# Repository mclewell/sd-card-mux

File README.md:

# SD-Card-Mux
A tool to automate testing SD-Card images on embedded devices.

When developing images for embedded devices, do you often find yourself 
constanly moving the SD-Card between the embedded device and development
computer? Surely there is a way to automate this switching...

The SD-Card Mux sits between the host development computer and an
embedded device, such as a Beaglebone Black, and allows an SD-Card to be 
programatically switched between the two.

The board uses a USB hub (U2640) that contains an SD-Card/MMC interface. A
standard micro-SD Card connects to this interface. One of the other USB ports 
on the hub connects to a USB-UART bridge (CP2102N). This bridge prodives a UART 
interface to the DUT and also controls the switching on the mux (TS3A27518E) 
using the GPIO on the bridge. The GPIO is controlled by the host computer 
using ```libgpiod```. 

Normally, the SD-Card is connected to the host computer. An image that is to be
booted by the DUT is written to the SD-Card. Instead of manually removing the 
card and inserting it into the DUT, a simple script can be added to the 
software development tooling to switch the card from the host computer to the 
embedded DUT.

## Usage
The SD-Card-Mux switching can be either controlled via software or manually
using the switch (```SW1```) on the top of the board.

### Software Control
Prerequisite: ```libgpiod```

Ubuntu:
```
sudo apt install libgpiod libgpiod-dev
```

Arch: Install from the AUR: 
```
https://aur.archlinux.org/packages/libgpiod/
```

1. Set SW2 (bottom left corner) to 'HW'. (**Note:** Silkscreen labels
on the board are backwards)
2. Insert a micro-sd card into J4.
3. Insert the sd-card-mux into the micro-sd card slot of the development board.
4. Connect a micro-USB cable between the sd-card-mux and development PC.
5. On power-up the sd-card-mux will route the SD card to the DUT, as denoted by the
illuminated LED by the micro-sd protrusion.
6. To switch the SD card to the development PC:
	
	6a. Find the GPIO controller name of the CP210N:
	```
	$ sudo gpiodetect
	gpiochip0 [INT34BB:00] (312 lines)
	gpiochip1 [cp210x] (4 lines)
	```
	6b. The mux control line is on ```GPIO.0```. To switch,
	```
	$ sudo gpioset gpiochip1 0=0
	```
	The LED next to the micro-sd card slot will blink when the SD-Card is
	accessed.

#### UART and Additional GPIO
The SD-Card-Mux also contains a USB-UART serial bridge. Conect the ```TXD```
and ```RXD``` signals in J2 to the UART on the DUT. The bridge should appear
on the development computer as ```/dev/ttyUSB0```.

There are also two additional GPIO from the CP210N broken out into the J2 
header (```GPIO.2```, ```GPIO.3```). These signals can be controlled in the same
fashion as the mux switch function using ```gpioset```. One of these lines can
be connected to the reset of the DUT. Ideally, the DUT should be held in reset
while the SD-card is switched. Once switched over, the reset line can be released
allowing the DUT to boot the new image. 

### Manual Control
1. Set SW2 to the 'SW' position. (**Note:** Silkscreen labels on the board are
backwards)
2. Use SW1 to switch the micro-SD card between the DUT and development 
computer. (**Note:** the silkscreen labels are also backwards here).

# Acknowledgements
- https://wiki.tizen.org/SDWire
- https://github.com/kopasiak/sd-mux

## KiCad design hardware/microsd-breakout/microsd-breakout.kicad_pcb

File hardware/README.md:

# Development Features
Since this was the first hardware spin of the board, some
development features were included.

## Software Switching
The software switching controlled through the CP210N GPIO control
the enable lines of two high-side power switches (```U7```/```U8```).
Only one of these switches should be enabled at a time, therefore the 
complementary output of ```U10``` is used. I had concerns that there
wouldn't be enough 'downtime' during the switch event to allow the 
on-board micro-sd card to fully powerdown before switching. 

The ```U10``` mux can be bypassed by using a GPIO.1 on the CP201N as 
the complementary switching singal. 
- Remove ```R12``` and ```R23```
- Install ```R11``` and ```R22```

During my testing, I have not seen any issues using the single mux
switch control line and mux complementary out.

## DUT Connection via FFC
A Flex-Flex Cable (FFC) header (```J3```) is provided to allow connections
to the DUT via a flex cable. The other end of the cable is connected to a
micro-sd breakout board, which is provided in this repo 
[here](microsd-breakout).

# Known Issues
- Silkscreen labels on ```S1``` and ```SW2``` are reversed.
- On-board micro-sd card in ```J4``` protrudes over the board edge
and may interfer with the DUT.
- The USB ESD protection (```D1```) caused the USB hub to fail to enumerate
at high-speed modes, full-speed works correctly. Removing ```D1``` solves
this issue.

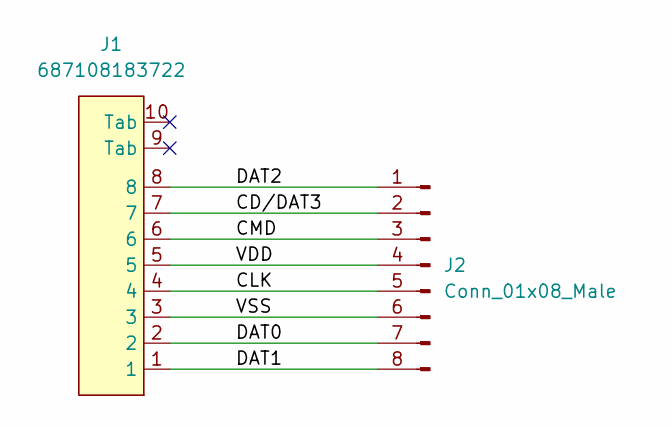
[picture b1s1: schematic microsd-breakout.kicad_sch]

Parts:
J1: 687108183722; Wurth_FPC_687108183722; PartNumber 687108183722
J2: Conn_01x08_Male; micro-sd-contacts

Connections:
/CD/DAT3: J1.7, J2.2
/CLK: J1.4, J2.5
/CMD: J1.6, J2.3
/DAT0: J1.2, J2.7
/DAT1: J1.1, J2.8
/DAT2: J1.8, J2.1
/VDD: J1.5, J2.4
/VSS: J1.3, J2.6

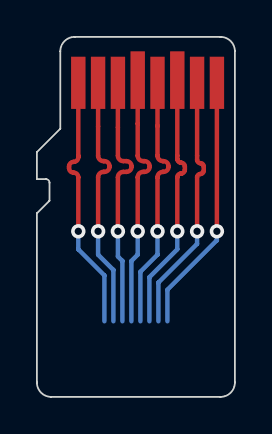
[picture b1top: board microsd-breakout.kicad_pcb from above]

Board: 2 copper layers, 11.0 x 20.0 mm, 3 parts (1 on the bottom side), 8 nets.

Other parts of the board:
REF1: Tab

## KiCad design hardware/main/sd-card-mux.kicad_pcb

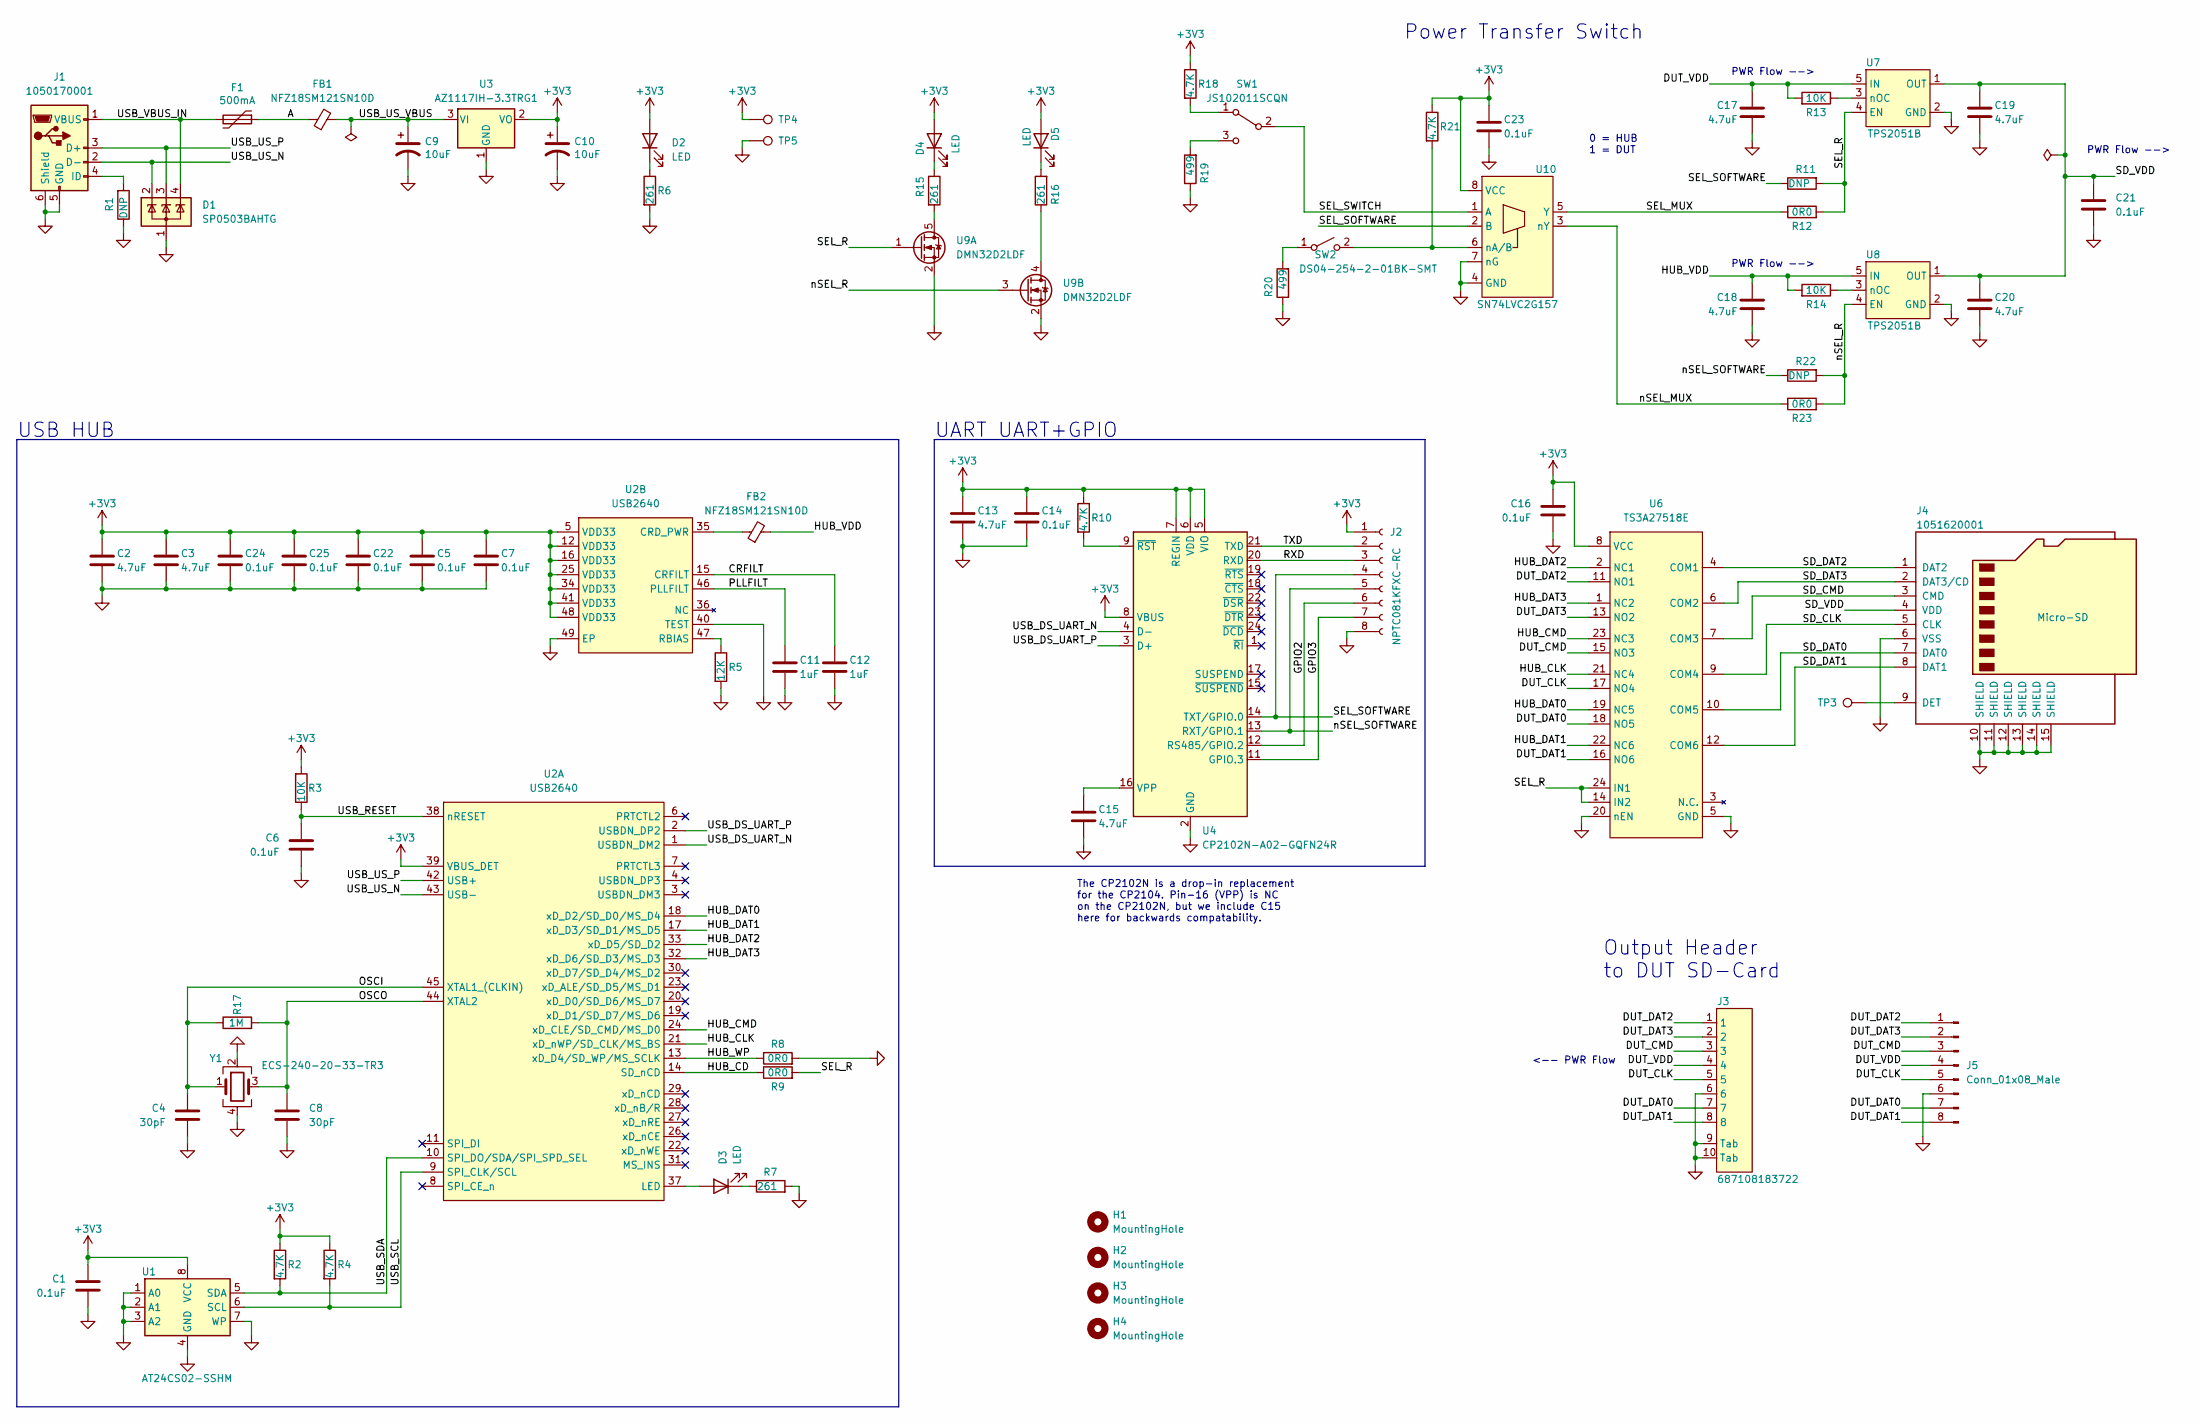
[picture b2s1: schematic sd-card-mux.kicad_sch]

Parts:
C1, C5, C6, C7, C14, C16, C21, C22, C23, C24, C25: 0.1uF; C_0603_1608Metric
C2, C3, C13, C15, C17, C18, C19, C20: 4.7uF; C_0603_1608Metric
C4, C8: 30pF; C_0603_1608Metric
C9, C10: 10uF; CP_EIA-3216-18_Kemet-A; PartNumber TAJA106K016SNJ
C11, C12: 1uF; C_0603_1608Metric
D1: SP0503BAHTG; SOT-143; PartNumber SP0503BAHTG
D2, D3, D4, D5: LED; LED_1206_3216Metric_Castellated
F1: 500mA; Fuse_1206_3216Metric_Castellated; PartNumber PTS120615V050
FB1, FB2: ‎NFZ18SM121SN10D‎; L_0603_1608Metric; PartNumber ‎NFZ18SM121SN10D‎
H1, H2, H3, H4: MountingHole; MountingHole_3.2mm_M3
J1: 1050170001; USB_Micro-B_Molex-105017-0001; PartNumber 1050170001
J2: NPTC081KFXC-RC; PinSocket_1x08_P2.54mm_Vertical_SMD_Pin1Right; PartNumber NPTC081KFXC-RC
J3: 687108183722; Wurth_FPC_687108183722; PartNumber 687108183722
J4: Micro-SD; micro-sd; PartNumber 1051620001
J5: Conn_01x08_Male; micro-sd-contacts
R1, R11, R22: DNP; R_0603_1608Metric
R2, R4, R10, R18, R21: 4.7K; R_0603_1608Metric
R3, R13, R14: 10K; R_0603_1608Metric
R5: 12K; R_0603_1608Metric
R6, R7, R15, R16: 261; R_0603_1608Metric
R8, R9, R12, R23: 0R0; R_0603_1608Metric
R17: 1M; R_0603_1608Metric
R19, R20: 499; R_0603_1608Metric
SW1: JS102011SCQN; CK_Switch_JS102011SCQN; PartNumber JS102011SCQN
SW2: DS04-254-2-01BK-SMT; CUI_DEVICES_DS04-254-2-01BK-SMT; PartNumber DS04-254-2-01BK-SMT
TP3: TestPoint; TestPoint_Pad_D1.0mm
TP4, TP5: TestPoint; test_point_RCSCTE; PartNumber RCSCTE
U1: AT24CS02-SSHM; SOIC-8_3.9x4.9mm_P1.27mm; PartNumber AT24CS02-SSHM-B
U2: USB2640; VQFN-48; PartNumber USB2640-HZH-02
U3: AZ1117IH-3.3TRG1; SOT-223-3_TabPin2; PartNumber AZ1117IH-3.3TRG1
U4: CP2102N-A02-GQFN24R; QFN-24-1EP_4x4mm_P0.5mm_EP2.6x2.6mm; PartNumber CP2102N-A02-GQFN24R
U6: TS3A27518E; TI_PW; PartNumber TS3A27518EPWR
U7, U8: TPS2051B; SOT-23-5; PartNumber TPS2051BDBVR
U9: DMN32D2LDF; SOT-353_SC-70-5; PartNumber DMN32D2LDF-7
U10: SN74LVC2G157; VSSOP-8_2.3x2mm_P0.5mm; PartNumber SN74LVC2G157DCU3
Y1: ECS-240-20-33-TR3; Crystal_SMD_Abracon_ABM8G-4Pin_3.2x2.5mm; PartNumber ECS-240-20-33-TR3

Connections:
+3V3: C1.2, C2.1, C3.1, C5.1, C7.1, C10.1, C13.1, C14.1, C16.2, C22.1, C23.1, C24.1, C25.1, D2.2 (A), D4.2 (A), D5.2 (A), J2.1, R2.1, R3.2, R4.1, R10.1, R18.1, R21.1, TP4.1, U1.8 (VCC), U2.5 (VDD33), U2.12 (VDD33), U2.16 (VDD33), U2.25 (VDD33), U2.34 (VDD33), U2.39 (VBUS_DET), U2.41 (VDD33), U2.48 (VDD33), U3.2 (VO), U4.5 (VIO), U4.6 (VDD), U4.7 (REGIN), U4.8 (VBUS), U6.8 (VCC), U10.8 (VCC)
/A: F1.1, FB1.1
/CRFILT: C12.1, U2.15 (CRFILT)
/DUT_CLK: J3.5, J5.5, U6.17 (NO4)
/DUT_CMD: J3.3, J5.3, U6.15 (NO3)
/DUT_DAT0: J3.7, J5.7, U6.18 (NO5)
/DUT_DAT1: J3.8, J5.8, U6.16 (NO6)
/DUT_DAT2: J3.1, J5.1, U6.11 (NO1)
/DUT_DAT3: J3.2, J5.2, U6.13 (NO2)
/DUT_VDD: C17.1, J3.4, J5.4, R13.2, U7.5 (IN)
/GPIO2: J2.6, U4.12 (RS485/GPIO.2)
/GPIO3: J2.7, U4.11 (GPIO.3)
/HUB_CD: R9.1, U2.14 (SD_nCD)
/HUB_CLK: U2.21 (xD_nWP/SD_CLK/MS_BS), U6.21 (NC4)
/HUB_CMD: U2.24 (xD_CLE/SD_CMD/MS_D0), U6.23 (NC3)
/HUB_DAT0: U2.18 (xD_D2/SD_D0/MS_D4), U6.19 (NC5)
/HUB_DAT1: U2.17 (xD_D3/SD_D1/MS_D5), U6.22 (NC6)
/HUB_DAT2: U2.33 (xD_D5/SD_D2), U6.2 (NC1)
/HUB_DAT3: U2.32 (xD_D6/SD_D3/MS_D3), U6.1 (NC2)
/HUB_VDD: C18.1, FB2.2, R14.2, U8.5 (IN)
/HUB_WP: R8.1, U2.13 (xD_D4/SD_WP/MS_SCLK)
/OSCI: C4.2, R17.1, U2.45 (XTAL1_(CLKIN)), Y1.1
/OSCO: C8.1, R17.2, U2.44 (XTAL2), Y1.3
/PLLFILT: C11.1, U2.46 (PLLFILT)
/RXD: J2.3, U4.20 (RXD)
/SD_CLK: J4.5 (CLK), U6.9 (COM4)
/SD_CMD: J4.3 (CMD), U6.7 (COM3)
/SD_DAT0: J4.7 (DAT0), U6.10 (COM5)
/SD_DAT1: J4.8 (DAT1), U6.12 (COM6)
/SD_DAT2: J4.1 (DAT2), U6.4 (COM1)
/SD_DAT3: J4.2 (DAT3/CD), U6.6 (COM2)
/SD_VDD: C19.1, C20.1, C21.2, J4.4 (VDD), U7.1 (OUT), U8.1 (OUT)
/SEL_MUX: R12.1, U10.5 (Y)
/SEL_R: R9.2, R11.2, R12.2, U6.14 (IN2), U6.24 (IN1), U7.4 (EN), U9.1 (G1)
/SEL_SOFTWARE: J2.4, R11.1, U4.14 (TXT/GPIO.0), U10.2 (B)
/SEL_SWITCH: SW1.2 (B), U10.1 (A)
/TXD: J2.2, U4.21 (TXD)
/USB_DS_UART_N: U2.1 (USBDN_DM2), U4.4 (D-)
/USB_DS_UART_P: U2.2 (USBDN_DP2), U4.3 (D+)
/USB_RESET: C6.2, R3.1, U2.38 (nRESET)
/USB_SCL: R4.2, U1.6 (SCL), U2.9 (SPI_CLK/SCL)
/USB_SDA: R2.2, U1.5 (SDA), U2.10 (SPI_DO/SDA/SPI_SPD_SEL)
/USB_US_N: D1.2 (K), J1.2 (D-), U2.43 (USB-)
/USB_US_P: D1.3 (K), J1.3 (D+), U2.42 (USB+)
/USB_US_VBUS: C9.1, FB1.2, U3.3 (VI)
/USB_VBUS_IN: D1.4 (K), F1.2, J1.1 (VBUS)
/nSEL_MUX: R23.1, U10.3 (nY)
/nSEL_R: R22.2, R23.2, U8.4 (EN), U9.3 (G2)
/nSEL_SOFTWARE: J2.5, R22.1, U4.13 (RXT/GPIO.1)
GND: C1.1, C2.2, C3.2, C4.1, C5.2, C6.1, C7.2, C8.2, C9.2, C10.2, C11.2, C12.2, C13.2, C14.2, C15.2, C16.1, C17.2, C18.2, C19.2, C20.2, C21.1, C22.2, C23.2, C24.2, C25.2, D1.1 (A), J1.5 (GND), J1.6 (Shield), J2.8, J3.6, J3.9 (Tab), J3.10 (Tab), J4.6 (VSS), J4.10 (SHIELD), J4.11 (SHIELD), J4.12 (SHIELD), J4.13 (SHIELD), J4.14 (SHIELD), J4.15 (SHIELD), J5.6, R1.1, R5.2, R6.2, R7.2, R8.2, R19.1, R20.1, TP5.1, U1.1 (A0), U1.2 (A1), U1.3 (A2), U1.4 (GND), U1.7 (WP), U2.40 (TEST), U2.49 (EP), U3.1 (GND), U4.2 (GND), U4.25 (GND), U6.5 (GND), U6.20 (nEN), U7.2 (GND), U8.2 (GND), U9.2 (S), U10.4 (GND), U10.7 (nG), Y1.2, Y1.4
unnamed: C15.1, U4.16 (VPP)
unnamed: D2.1 (K), R6.1
unnamed: D3.1 (K), R7.1
unnamed: D3.2 (A), U2.37 (LED)
unnamed: D4.1 (K), R15.1
unnamed: D5.1 (K), R16.2
unnamed: FB2.1, U2.35 (CRD_PWR)
unnamed: J1.4 (ID), R1.2
unnamed: J4.9 (DET), TP3.1
unnamed: R5.1, U2.47 (RBIAS)
unnamed: R10.2, U4.9 (~RST)
unnamed: R13.1, U7.3 (nOC)
unnamed: R14.1, U8.3 (nOC)
unnamed: R15.2, U9.5 (D1)
unnamed: R16.1, U9.4 (D2)
unnamed: R18.2, SW1.1 (A)
unnamed: R19.2, SW1.3 (C)
unnamed: R20.2, SW2.1 (A)
unnamed: R21.2, SW2.2 (B), U10.6 (nA/B)

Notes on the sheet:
The CP2102N is a drop-in replacement for the CP2104. Pin-16 (VPP) is NC on the CP2102N, but we include C15 here for backwards compatability.
Power Transfer Switch
0 = HUB 1 = DUT
<-- PWR Flow
PWR Flow -->
Output Header to DUT SD-Card
USB HUB
UART UART+GPIO

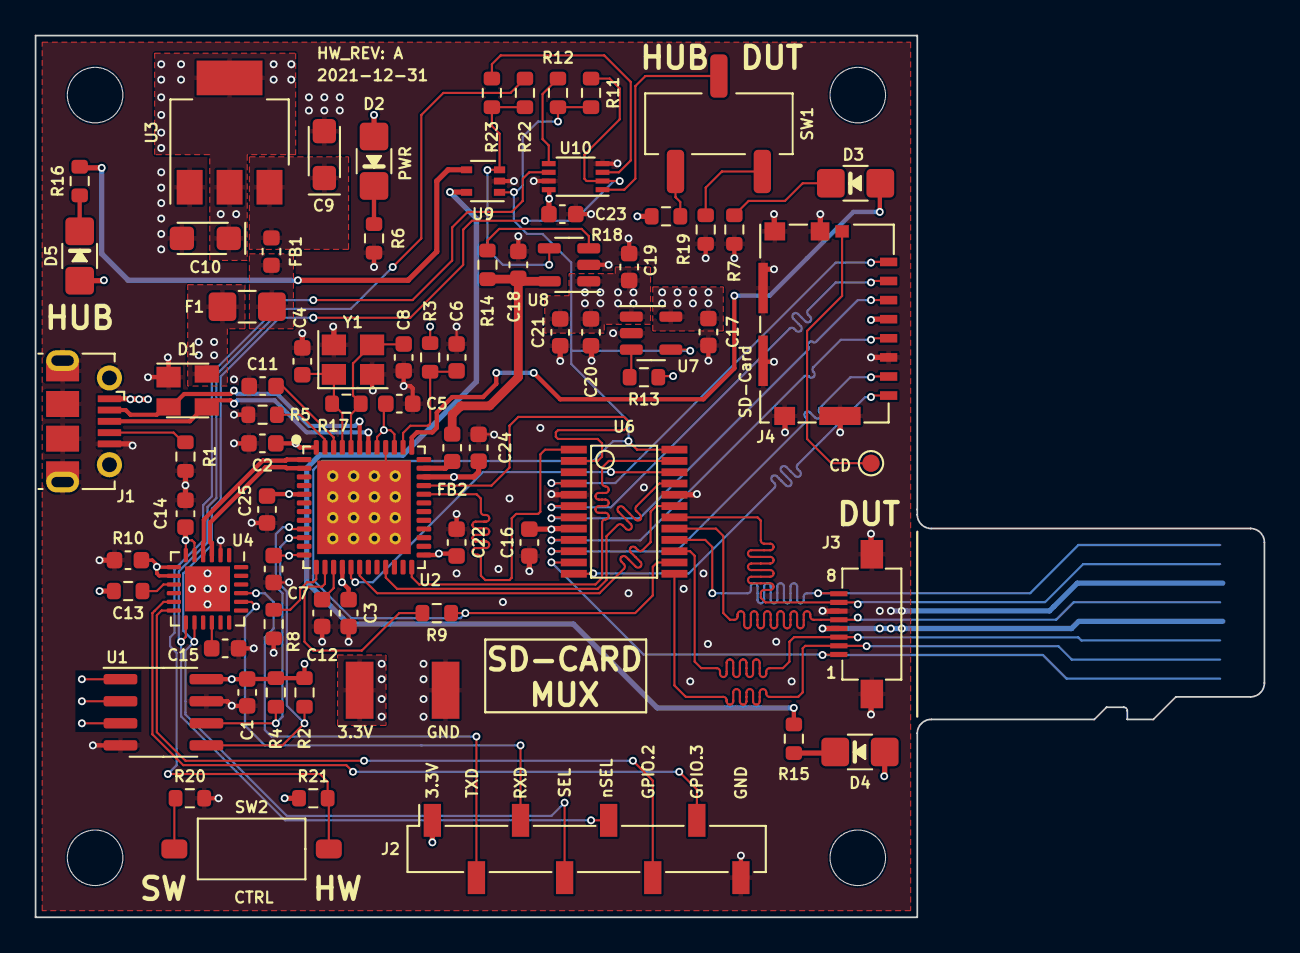
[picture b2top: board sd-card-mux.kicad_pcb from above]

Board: 4 copper layers, 70.8 x 50.8 mm, 80 parts (1 on the bottom side), 69 nets.

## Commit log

2022-01-03 Updated PCB gerber generation settings and add gerbers.
2022-01-13 Added breakout board for micro-sd
2022-01-23 Added breakout board and documentation.
2022-01-23 Updated documentation
2022-01-23 Fixed documentation typos
2022-01-23 Fixed documentation link
2022-01-23 Added panel documentation
2022-01-23 Added D1 errata
